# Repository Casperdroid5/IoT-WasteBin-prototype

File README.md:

# WasteBin Project

Het WasteBin Project, ook bekend als de Slimme Vuilnisbak, heeft als doel het probleem van onaangename geuren in kleine leefruimtes, zoals appartementen, aan te pakken, terwijl het efficiënte afvalscheiding en milieubehoud bevordert.

Door de ontwikkeling van een uniek apparaat voorkomt dit project niet alleen onaangename geuren, maar stimuleert het ook gebruikers om verschillende soorten afval te scheiden, wat leidt tot effectievere recycling en een verminderde milieubelasting.

Dit project is ontwikkeld voor [Insyte Technology](https://insyte-technology.nl/).

Please note that the Dutch text provided above translates to English as follows:

# WasteBin Project

The WasteBin Project, also known as the Smart Wastebin, aims to tackle the problem of unpleasant odors in small living spaces, such as apartments, while promoting efficient waste separation and environmental conservation.

By developing a unique device, this project not only prevents unpleasant odors but also encourages users to separate different types of waste, leading to more effective recycling and reduced environmental impact.

This project was developed for [Insyte Technology](https://insyte-technology.nl/).

Please note that most of the text is written in Dutch on request of the company.

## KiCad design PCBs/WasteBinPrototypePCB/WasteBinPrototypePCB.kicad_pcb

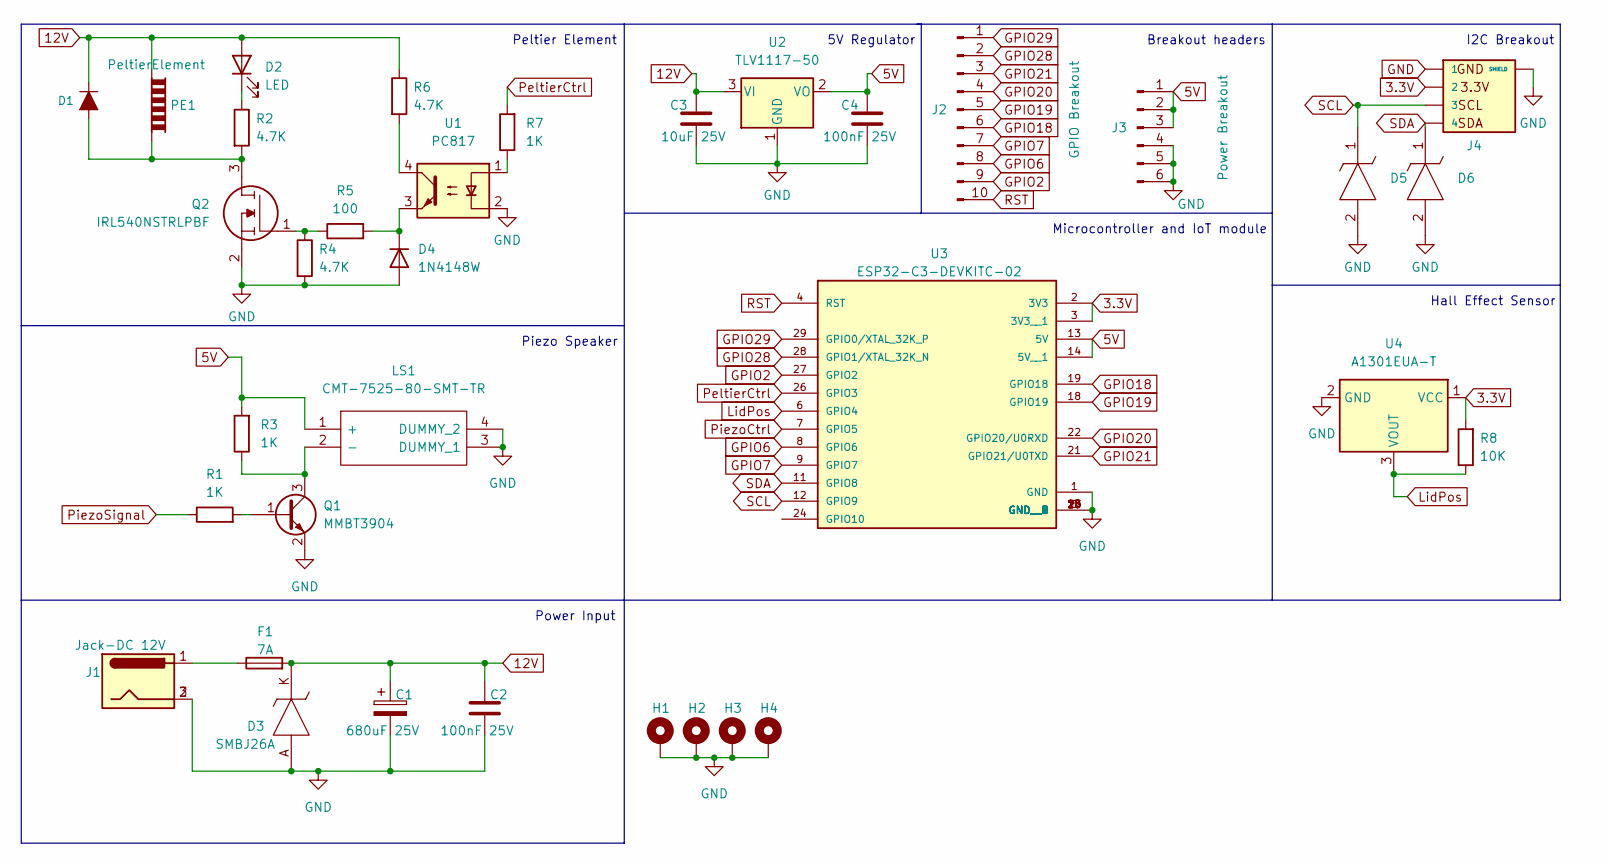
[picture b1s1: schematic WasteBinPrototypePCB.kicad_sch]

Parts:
C1: 680uF 25V; CP_Elec_8x10; Manufacturer_Part_Number C3339; LCSC C445063
C2, C4: 100nF 25V; C_0805_2012Metric_Pad1.18x1.45mm_HandSolder; LCSC C476766
C3: 10uF 25V; C_0805_2012Metric_Pad1.18x1.45mm_HandSolder; Manufacturer_Part_Number C9807; LCSC C15850
D1: DIODE-1N4148; D_1206_3216Metric_Pad1.42x1.75mm_HandSolder; LCSC C2128
D2: LED; LED_0805_2012Metric_Pad1.15x1.40mm_HandSolder
D3: SMBJ26A; DIOM5436X261N; Mouser Part Number 652-SMBJ26A
D4: 1N4148W; D_SOD-123
D5, D6: ESD7351HT1G; SOD2512X110N; Mouser Part Number 863-ESD7351HT1G
F1: 7A; Fuse_2010_5025Metric_Pad1.52x2.65mm_HandSolder; LCSC C136353
H1, H2, H3, H4: MountingHole_Pad; MountingHole_3.2mm_M3
J1: Jack-DC 12V; BarrelJack_Wuerth_6941xx301002; Mouser 710-694106301002
J2: Conn_01x10_Male; PinSocket_1x10_P2.54mm_Vertical
J3: Conn_01x06_Male; PinSocket_1x06_P2.54mm_Vertical
J4: SM04B-SRSS-TB(LF)(SN); JST_SM04B-SRSS-TB(LF)(SN); LCSC C160404
LS1: CMT-7525-80-SMT-TR; CMT752580SMTTR; Mouser Part Number 490-CMT-7525-80SMTTR
PE1: PeltierElement; TerminalBlock_bornier-2_P5.08mm; Mouser 651-1808190
Q1: MMBT3904; SOT-23
Q2: IRL540NSTRLPBF; IRF2804STRLPBF; Mouser Part Number 942-IRL540NSTRLPBF
R1, R3, R7: 1K; R_0805_2012Metric_Pad1.20x1.40mm_HandSolder
R2, R4, R6: 4.7K; R_0805_2012Metric_Pad1.20x1.40mm_HandSolder
R5: 100; R_0805_2012Metric_Pad1.20x1.40mm_HandSolder
R8: 10K; R_0805_2012Metric_Pad1.20x1.40mm_HandSolder
U1: PC817; DIP-4_W7.62mm
U2: TLV1117-50; SOT230P700X180-4N
U3: ESP32-C3-DEVKITC-02; XCVR_ESP32-C3-DEVKITC-02
U4: A1301EUA-T; PinSocket_1x03_P2.54mm_Vertical

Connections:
3.3V: J4.2, R8.2, U3.2 (3V3), U3.3 (3V3__1), U4.1 (VCC)
5V: C4.2, J3.1, J3.2, J3.3, LS1.1 (+), R3.2, U2.2 (VO), U3.13 (5V), U3.14 (5V__1)
12V: C1.1, C2.1, C3.1, D1.1 (C), D2.2 (A), D3.K, F1.2, PE1.1, R6.1, U2.3 (VI)
GND: C1.2, C2.2, C3.2, C4.1, D3.A, D4.2 (A), D5.2, D6.2, H1.1, H2.1, H3.1, H4.1, J1.2, J1.3, J3.4, J3.5, J3.6, J4.1, J4.S1 (SHIELD), J4.S2 (SHIELD), LS1.3 (DUMMY_1), LS1.4 (DUMMY_2), Q1.2 (E), Q2.2, R4.2, U1.2, U2.1 (GND), U3.1 (GND), U3.5 (GND__1), U3.10 (GND__2), U3.15 (GND__3), U3.16 (GND__4), U3.17 (GND__5), U3.20 (GND__6), U3.23 (GND__7), U3.25 (GND__8), U3.30 (GND__9), U4.2 (GND)
GPIO2: J2.9, U3.27 (GPIO2)
GPIO6: J2.8, U3.8 (GPIO6)
GPIO7: J2.7, U3.9 (GPIO7)
GPIO18: J2.6, U3.19 (GPIO18)
GPIO19: J2.5, U3.18 (GPIO19)
GPIO20: J2.4, U3.22 (GPIO20/U0RXD)
GPIO21: J2.3, U3.21 (GPIO21/U0TXD)
GPIO28: J2.2, U3.28 (GPIO1/XTAL_32K_N)
GPIO29: J2.1, U3.29 (GPIO0/XTAL_32K_P)
LidPos: R8.1, U3.6 (GPIO4), U4.3 (VOUT)
unnamed: D1.2 (A), PE1.2, Q2.3, R2.2
unnamed: D2.1 (K), R2.1
unnamed: D4.1 (K), R5.2, U1.3
unnamed: F1.1, J1.1
unnamed: Q1.1 (B), R1.2
unnamed: LS1.2 (-), Q1.3 (C), R3.1
unnamed: Q2.1, R4.1, R5.1
unnamed: R6.2, U1.4
unnamed: R7.1, U1.1
PeltierCtrl: R7.2, U3.26 (GPIO3)
PiezoCtrl: U3.7 (GPIO5)
PiezoSignal: R1.1
RST: J2.10, U3.4 (RST)
SCL: D5.1, J4.3, U3.12 (GPIO9)
SDA: D6.1, J4.4, U3.11 (GPIO8)

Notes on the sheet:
5V Regulator
Hall Effect Sensor
I2C Breakout
Peltier Element
Microcontroller and IoT module
Power Input
Piezo Speaker
Breakout headers

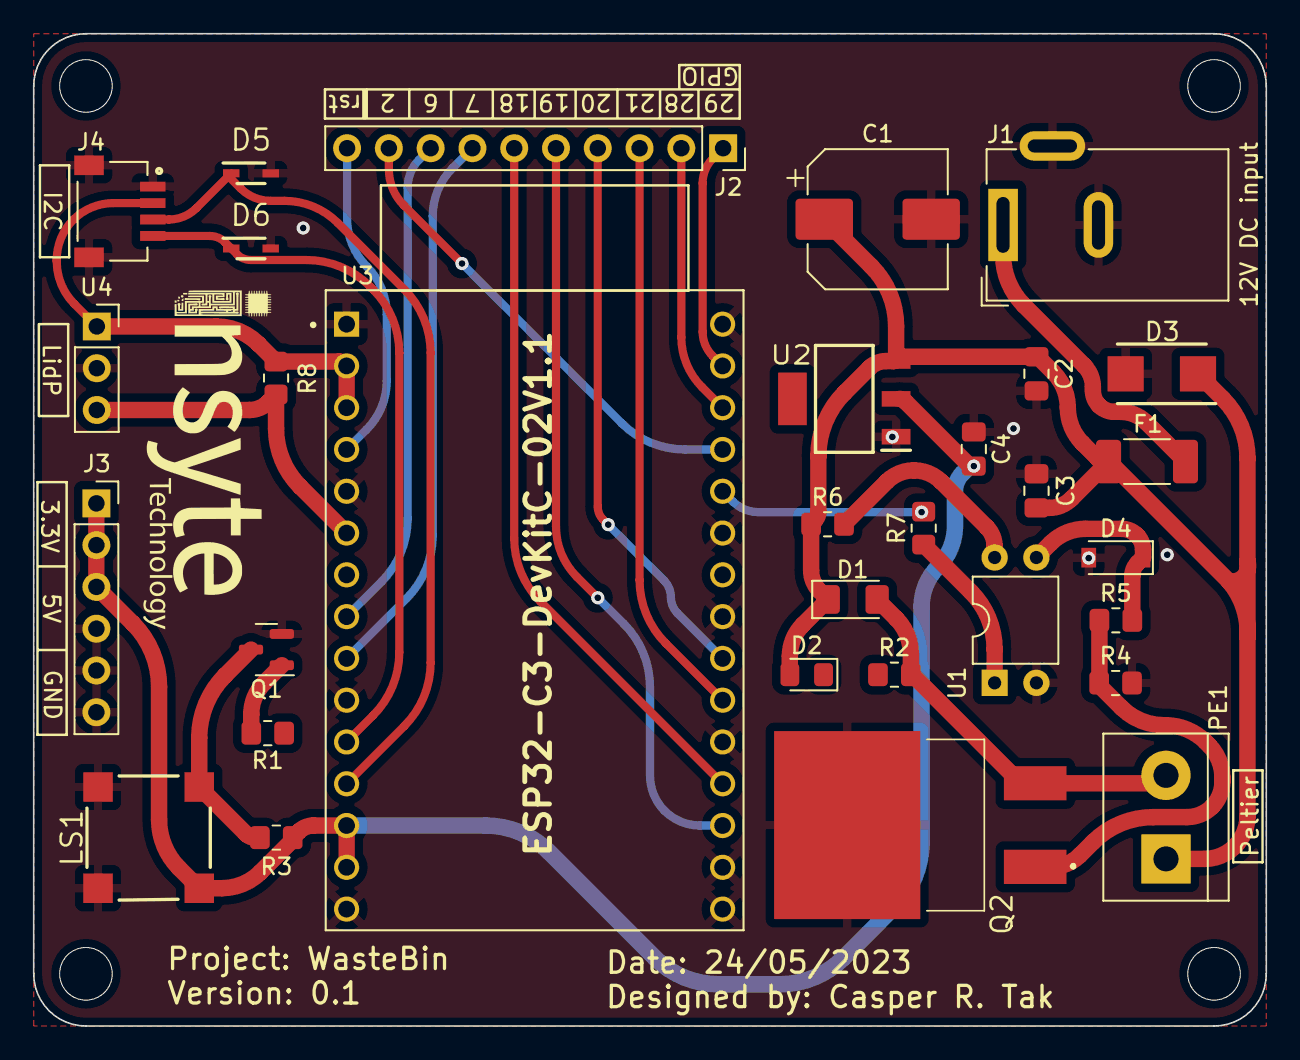
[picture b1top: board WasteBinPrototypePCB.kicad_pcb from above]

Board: 2 copper layers, 74.9 x 60.3 mm, 35 parts (0 on the bottom side), 27 nets.

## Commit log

2023-02-09 Use case diagram created
2023-02-09 Initial UCD
2023-02-09 WasteBin_UCD.puml added
2023-02-09 use case diagram
2023-02-09 Added empty input output schema
2023-02-09 changed naming
2023-02-09 Finished input output schema
2023-03-16 First commit of project
2023-03-16 combined temperature sensor and mqtt code.
2023-03-16 Code is now sending and recieving BMP390 sensor data to MQTT
2023-03-17 code now sends pressure and temperature data in one char array
2023-03-17 removed bug that prevented connection to mqtt server
2023-03-22 added litd lid position detection readings in code
2023-03-22 functional Node-Red with 2 charts and text for 1 esp32
2023-03-23 Added esp32tohivemq.txt with functional code for wastebin4
2023-03-23 removed esp32tohivemq.txt and transferd data to esp32tohivemq.ino
2023-03-24 Created functional local mqtt broker with coresponding code.
2023-03-24 changed names from ino files.
2023-03-24 removed all unused code
2023-04-12 added even more files
2023-04-12 added lidposition files and inplemented SHT40 sensor (not tested)
2023-04-12 added new files
2023-04-12 removed OOP
2023-04-12 added improved new version of original code. Does not contain sensors
2023-04-12 Improved code without sensors
2023-04-12 split code into main and .h file
2023-04-13 changed old program from bmp3XX to SHT40 sensor. Functional with node-red
2023-04-13 improved WasBinPrototypeSotware by writing to seperate topics.
2023-04-13 implemented sensor code into main WasteBinPrototypeSoftware. Also linked with nodeRed
2023-04-13 simple node-red flow added for latest software
2023-04-14 changed up main file to send data as a json string to 1 topic
2023-04-14 added macadress to payload
2023-04-14 made some minor improvements
2023-04-14 added new Node-Red/Multiple WasteBinPrototypeSotware flows.json that can support multiple WasteBins at the same time
2023-04-14 added code to control the peltier and fan modules.
2023-04-14 added neopixel (RGB LED) to sketch for visualisation purposes
2023-04-14 removed rgb code (it contained a bug that killed the temperature sensor)
2023-04-17 added control system for temperature control (peltier)
2023-04-21 Database added
2023-04-24 Added DatabaseIntegrationWithoutWasteBins.json databasesupport
2023-04-24 timestamp added to incomming data Node-Red
2023-04-25 added new database design ERD
2023-05-08 added modified Database design
2023-05-09 changed database to new draw.io design
2023-05-10 got database working manually
2023-05-10 Database integration functional, optimisation needed
2023-05-10 database structure completed for now. Database filled with data, no sensor data yet
2023-05-11 improved on modularity of wastebin software
2023-05-11 added doxygen commentary to code
2023-05-11 cleanup folder
2023-05-11 added piezo speaker code to main
2023-05-11 fixed the broken piezo speaker code.
2023-05-11 fixed the broken piezo speaker code, but now for real.
2023-05-11 started working on doxyfile
2023-05-12 created markdown IoT oplossing
2023-05-12 added database to IoT oplossing.md
2023-05-12 added bureaublad onderzoek.md en ontwerpkeuzes.md
2023-05-12 cleanup of repository
2023-05-12 improved heavily on the readme file
2023-05-12 added example documentation pdf (WasteBin.pdf)
2023-05-15 cleanup branch
2023-05-15 improved database, added columns and better datatypes
2023-05-15 added new data to database
2023-05-15 added new view to database
2023-05-17 fixed table error in testplan.md
2023-05-22 created PCB-design.md and improved on ontwerpkeuzes.md file
2023-05-22 Improvements made on documentation
2023-05-22 added pcb initialisation
2023-05-22 added peltier design to schematic
2023-05-22 added piezo speaker to schematic
2023-05-22 added Hall effect sensor to schematic
2023-05-24 improved on documentation and design
2023-05-24 added microcontroller, breakout headers, 5V regulator and i2c vreakout to schematic
2023-05-24 added Power input
2023-05-24 added name to power input section
2023-05-24 improved layout of schematic
2023-05-24 footprints assigned to each component
2023-05-24 started on pcb design
2023-05-24 grouped componentes
2023-05-24 added 3d models to components
2023-05-24 created pcb board outline, layed out components and starting retouing wires.
2023-05-24 finished wiring and added silkscreen.
2023-05-24 finished V0.1, waiting for feedback
2023-05-24 applied rounded tracks design
2023-05-25 improved and added on PCB-design.md documentation
2023-05-25 improved bureaubladonderoek
2023-05-25 added mosquitosetup.md
2023-05-25 translated Mosquittosetup to dutch
2023-05-25 improved on IoT solution database views
2023-05-25 removed image error
2023-05-25 improved formatting in Bureaubladonderzoek.md
2023-05-25 extended on testplan.md
2023-05-25 added database query's and tables
2023-05-25 improved IoT database solution
2023-05-25 improved iot .md
2023-05-25 removed the querys
2023-05-25 added all querys back
2023-05-25 improved on text
2023-05-25 added uml diagrams
2023-05-25 added newly generated report
2023-05-25 fixed github and removed settings
2023-05-25 removed latex files
2023-05-31 added mosquitto instellen file, it dissapeared
2023-05-31 added mosquitto config file settings
2023-05-31 small edits to file
2023-05-31 added new WasteBin ESE verslag document and doxyfile
2023-05-31 added new report (v0.3)
2023-06-08 added poster created by the IDE
2023-06-08 Updated poster
2023-06-08 removed documentation folder
